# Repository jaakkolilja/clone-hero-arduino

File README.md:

# Clone Hero Arduino Controller (Nano)

This project allows an **Arduino Nano** (or Nano Every) to function as a 9-button guitar controller for Clone Hero. Since the standard Nano does not support native keyboard emulation (HID), this project uses a **Python bridge** to read serial data and simulate keyboard inputs with minimal latency.

## Hardware Requirements
* **Arduino Nano**
* **9 Buttons** (5 Frets, Strum Up/Down, Start, Star Power)
* **9x 10k Ohm Resistors** (for Pull-down configuration)
* **Hookup wire** (approx. 1m for the neck)

## Wiring
* **Common 3.3V Rail:** A single 3.3V wire is daisy-chained to one pin of every button.
* **Signal Lines:** Each button's second pin is connected to an individual digital pin on the Arduino (**D2 through D10**).
* **Pull-down Resistors:** Each signal line (D2-D10) must be connected to **GND** via a 10k ohm resistor. This is crucial for long (1m) wires to prevent electrical noise and "ghost" inputs.

| Component | Arduino Pin |
| :--- | :--- |
| Green Fret | D2 |
| Red Fret | D3 |
| Yellow Fret | D4 |
| Blue Fret | D5 |
| Orange Fret | D6 |
| Strum Up | D7 |
| Strum Down | D8 |
| Star Power | D9 |
| Start / Menu | D10 |

## Software Setup

1. **Arduino:**
   - Upload the provided code to your Arduino.
   - The baud rate is set to `115200` to ensure high-speed communication.

2. **Python Environment:**
   - Install the required libraries using your terminal:
     ```bash
     pip install pyserial pydirectinput
     ```
   - Open `guitar.py` and ensure the `PORT` variable matches your Arduino's COM port (e.g., `'COM4'`).
   - You can customize key bindings in the `KEY_MAP` dictionary within the script.

## How to Use
1. Plug in your Arduino.
2. Run the Python script: `python guitar.py`.
3. Keep the script running in the background.
4. Open **Clone Hero** and press **Space** to enter the **Controller Settings**.
5. Map your physical buttons to the in-game actions.

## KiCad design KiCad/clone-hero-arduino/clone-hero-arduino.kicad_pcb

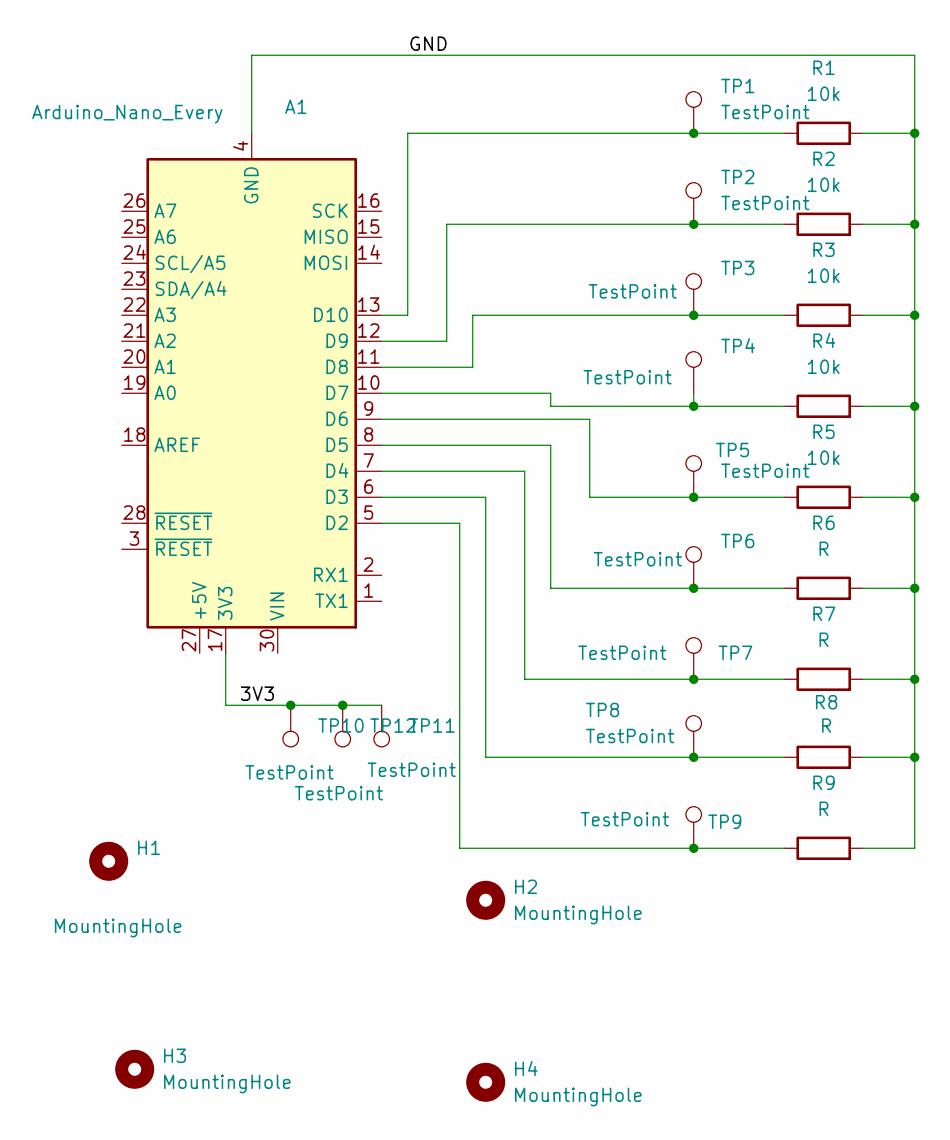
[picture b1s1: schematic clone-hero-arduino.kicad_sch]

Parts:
A1: Arduino_Nano_Every; Arduino_Nano
H1, H2, H3, H4: MountingHole; MountingHole_3.2mm_M3
R1, R2, R3, R4, R5: 10k; R_Axial_DIN0207_L6.3mm_D2.5mm_P7.62mm_Horizontal
R6, R7, R8, R9: R; R_Axial_DIN0207_L6.3mm_D2.5mm_P7.62mm_Horizontal
TP1, TP2, TP3, TP4, TP5, TP6, TP7, TP8, TP9, TP10, TP11, TP12: TestPoint; TestPoint_THTPad_D2.0mm_Drill1.0mm

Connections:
/3V3: A1.17 (3V3), TP10.1, TP11.1, TP12.1
/GND: A1.4 (GND), A1.29 (GND), R1.2, R2.2, R3.2, R4.2, R5.2, R6.2, R7.2, R8.2, R9.2
unnamed: A1.5 (D2), R9.1, TP9.1
unnamed: A1.6 (D3), R8.1, TP8.1
unnamed: A1.7 (D4), R7.1, TP7.1
unnamed: A1.8 (D5), R6.1, TP6.1
unnamed: A1.9 (D6), R5.1, TP5.1
unnamed: A1.10 (D7), R4.1, TP4.1
unnamed: A1.11 (D8), R3.1, TP3.1
unnamed: A1.12 (D9), R2.1, TP2.1
unnamed: A1.13 (D10), R1.1, TP1.1

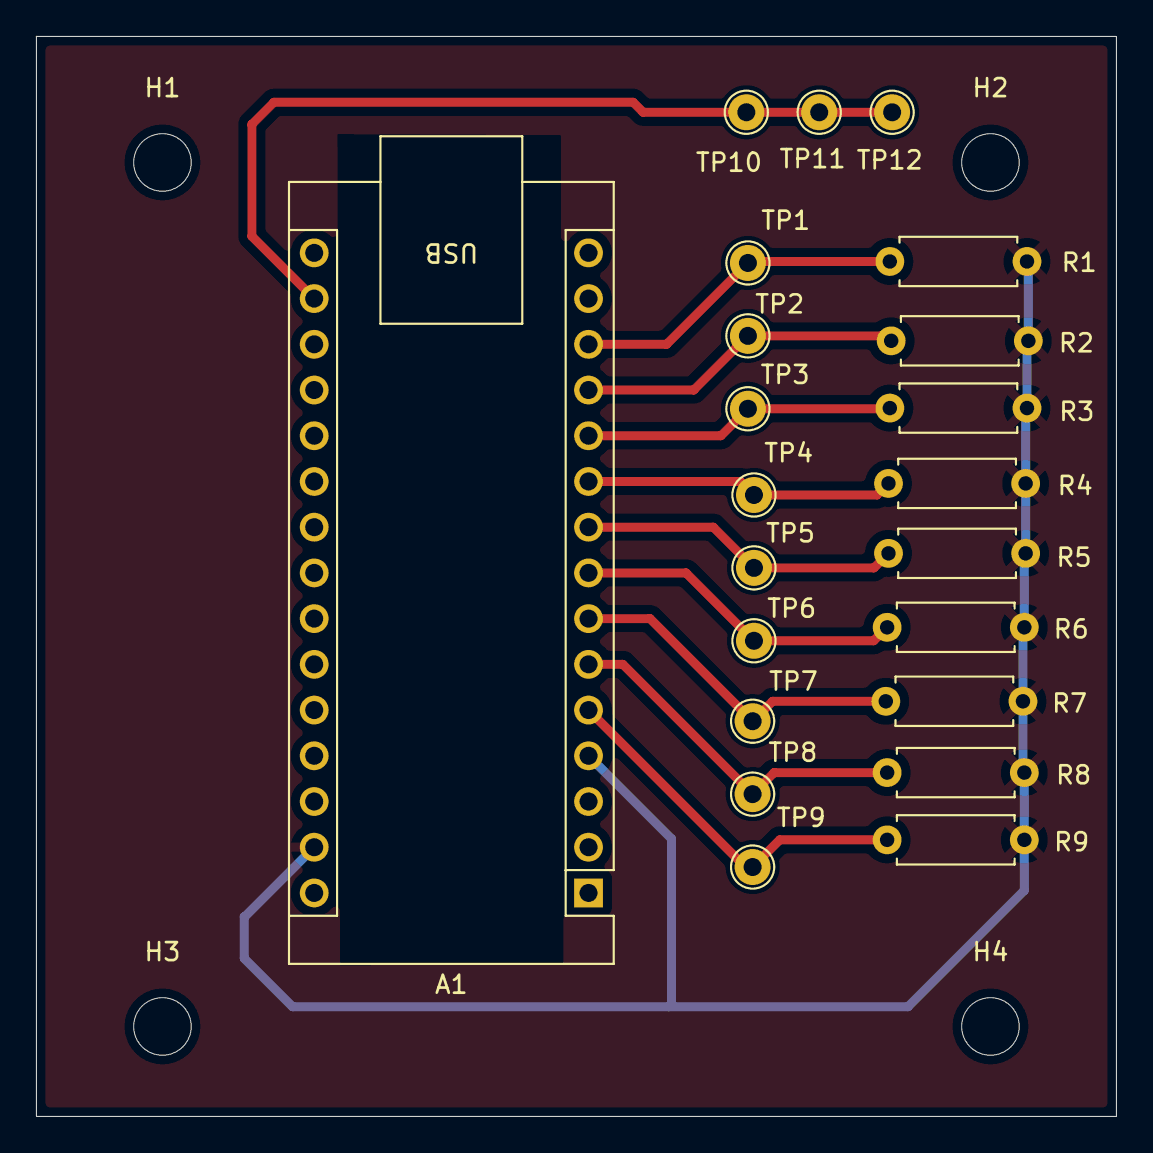
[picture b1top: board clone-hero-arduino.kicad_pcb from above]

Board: 2 copper layers, 60.0 x 60.0 mm, 26 parts (0 on the bottom side), 11 nets.

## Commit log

2026-02-21 python and arduino code
2026-02-21 removed .idea
2026-02-21 added readme
2026-02-21 upgraded code from 2 to 9 buttons
2026-02-22 added stl files for fretboard parts
2026-02-22 moved arduino file to root
2026-02-22 g file
2026-02-25 created a pcb design in Kicad
2026-02-25 made Kicad model
2026-02-25 added gitattributes file
2026-02-25 edited gitattributes
2026-02-26 updated stl files
2026-03-03 edited scripts
